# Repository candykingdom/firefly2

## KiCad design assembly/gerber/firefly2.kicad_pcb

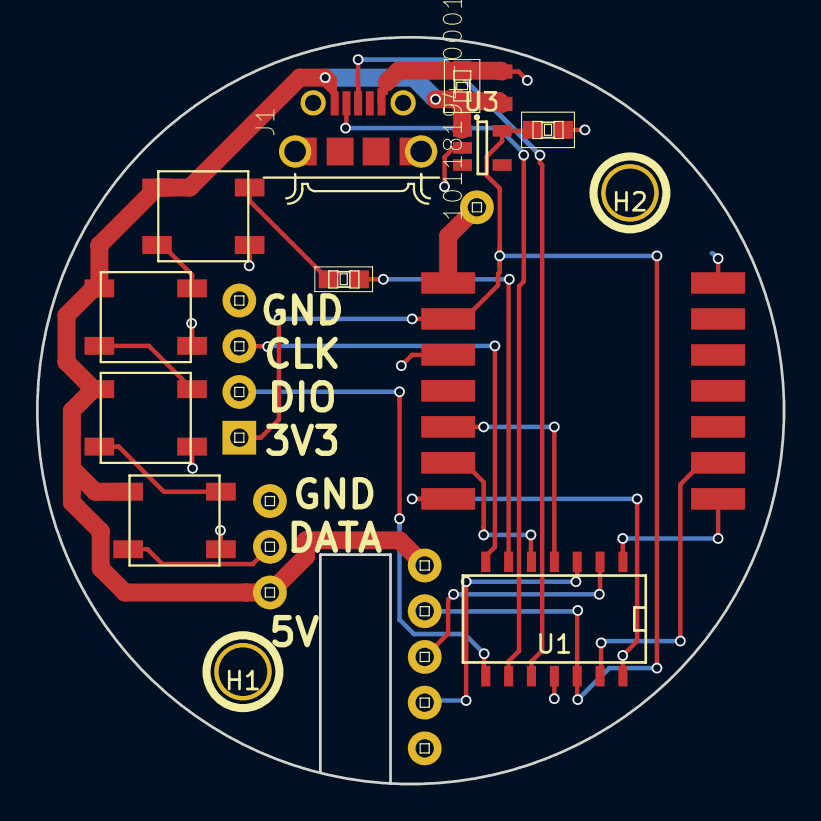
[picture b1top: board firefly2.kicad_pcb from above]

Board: 2 copper layers, 41.5 x 41.5 mm, 18 parts (0 on the bottom side), 21 nets.

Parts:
C1: 10uF; 0805
C2, C3: 1uF; 0603
D1, D2, D3, D4: WS2812B
H1, H2: hole; hole-m2.5
J1: 10118194-0001LF; FRAMATOME_10118194-0001LF
P2: CONN_01X03; 1X03
P3: CONN_01X04; 1X04
P4: CONN_01X05; 1X05
P5: CONN_01X01; 1X01
R1: 220; 0603
U1: SAM_D11C; SOIC-14_N
U2: RFM69CW; RFM69CW-XXXS2
U3: MIC5504; SOT-23-5

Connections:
+3V3: C3.2, P3.1, P4.2, U1.12, U2.2, U3.5
+5V: C1.2, C2.2, D1.1, D2.1, D3.1, D4.1, J1.1, P2.1, P4.1, U3.1
ANTENNA: P5.1, U2.1
ARM_SWCLK: P3.3, U1.7
ARM_SWDIO: P3.2, U1.8
AUX1: P4.3, U1.2
AUX2: P4.4, U1.3
GND: C1.1, C2.1, C3.1, D1.3, D2.3, D3.3, D4.3, J1.5, P2.3, P3.4, P4.5, U1.11, U2.3, U2.14, U3.2
LED_EXTERNAL: D4.2, P2.2
LED_INTERNAL: R1.1, U1.6
unnamed: D1.2, D2.4
unnamed: D1.4, R1.2
unnamed: D2.2, D3.4
unnamed: D3.2, D4.4
RADIO_DIO0: U1.13, U2.9
RADIO_MISO: U1.1, U2.8
RADIO_MOSI: U1.4, U2.5
RADIO_NSS: U1.14, U2.7
RADIO_SCK: U1.5, U2.6
USB_D+: J1.3, U1.10
USB_D-: J1.2, U1.9
